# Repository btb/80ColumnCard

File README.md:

# 80ColumnCard
An 80-Column Card for the Apple II, II+, and clones.

This is mostly a clone of the Videx Videoterm, with some changes to reduce the number of chips needed.

[Interactive BOM](https://btb.github.io/80ColumnCard/hardware/80ColumnCard/bom/80ColumnCard_0.html)

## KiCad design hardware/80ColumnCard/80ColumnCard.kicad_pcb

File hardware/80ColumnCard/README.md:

# 80ColumnCard

## Construction notes

## RAM (U10)
U10 is designed to use a 6116 Static RAM chip, however there are multiple overlapping footprints available on the board in order for you to just use whatever 2K or larger SRAM is easiest for you to obtain. Consult the interactive BOM if you're not sure how to place the chip. Many larger chips however have the A11 pin where the 6116 has the /WE pin, so you'll have to cut and then re-solder the X21 jumper accordingly.

## Firmware ROM (U3)
U3 holds the 1K of firmware (e.g. "Videx Videoterm ROM 2.4.bin") and can be any EPROM from a 2758A up to a 27(C)512, depending on whatever you have available. A10 will be permanently tied low, and A11-A15 are all permanently tied high, so the code needs to go in the lower 1K of a 2716, or the lower half of the top 2K of any larger EPROM. (Or just repeat it enough times to fill up the whole thing)

## Character ROM (U20)
Any size from 2732 to 27C512 (27C080 on rev0) is pin-compatible, however the character generator subcircuit appears to be very sensitive to the speed of this EPROM. Character corruption occurs with EPROMs that are too fast, so 200ns or slower (higher number) is recommended.
Confirmed working are: M27C64-20, AM2732A-2.

This EPROM can hold one or two of the 2K [character sets](../../character_roms). A12-A15 are all permanently tied high, so only the top 4K of the EPROM is usable. The standard character set (e.g. "videx std 7x9 - top right.bin") goes in the lower 2K of that space, and any desired alternative character set (e.g. "videx inverse - top left.bin") goes in the upper 2K of that space.

## Other
Although many of the TTL LS chips can be substituted with members of newer logic families (ACT, for example), U2 (74LS02) U4 (74LS04) U6 (74LS00) U23 (74LS161) must be LS or other TTL (non-CMOS) families.

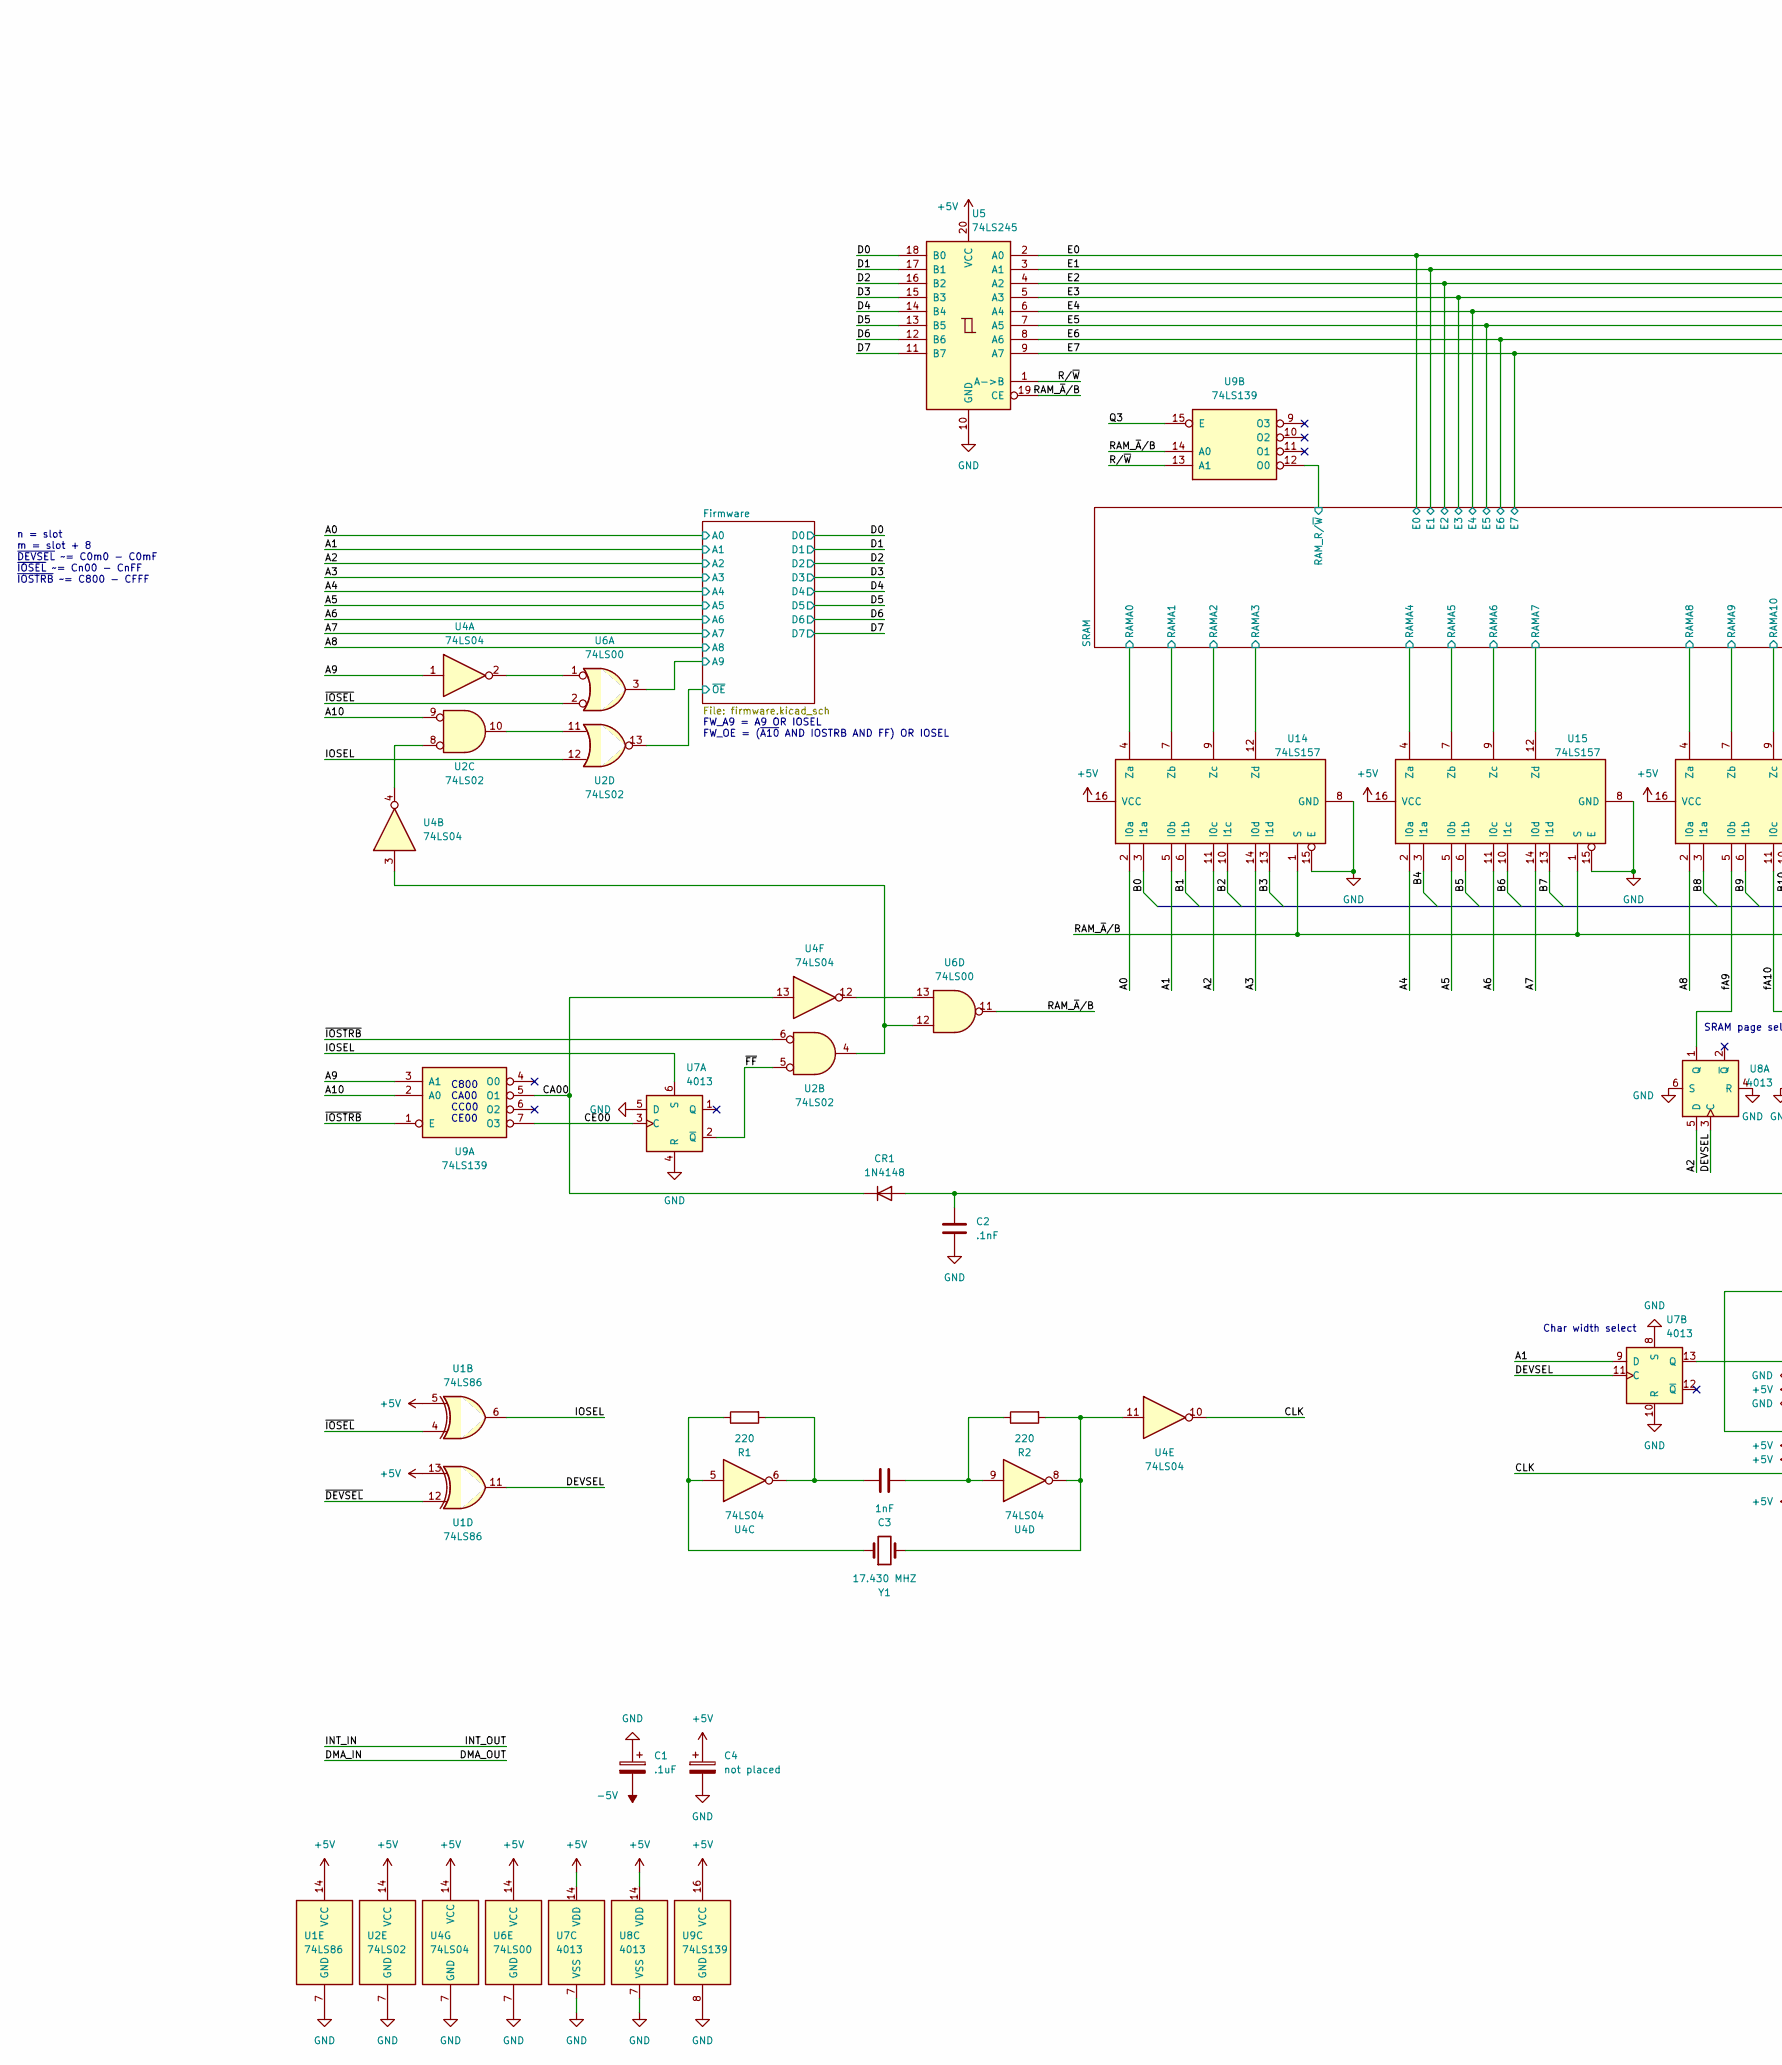
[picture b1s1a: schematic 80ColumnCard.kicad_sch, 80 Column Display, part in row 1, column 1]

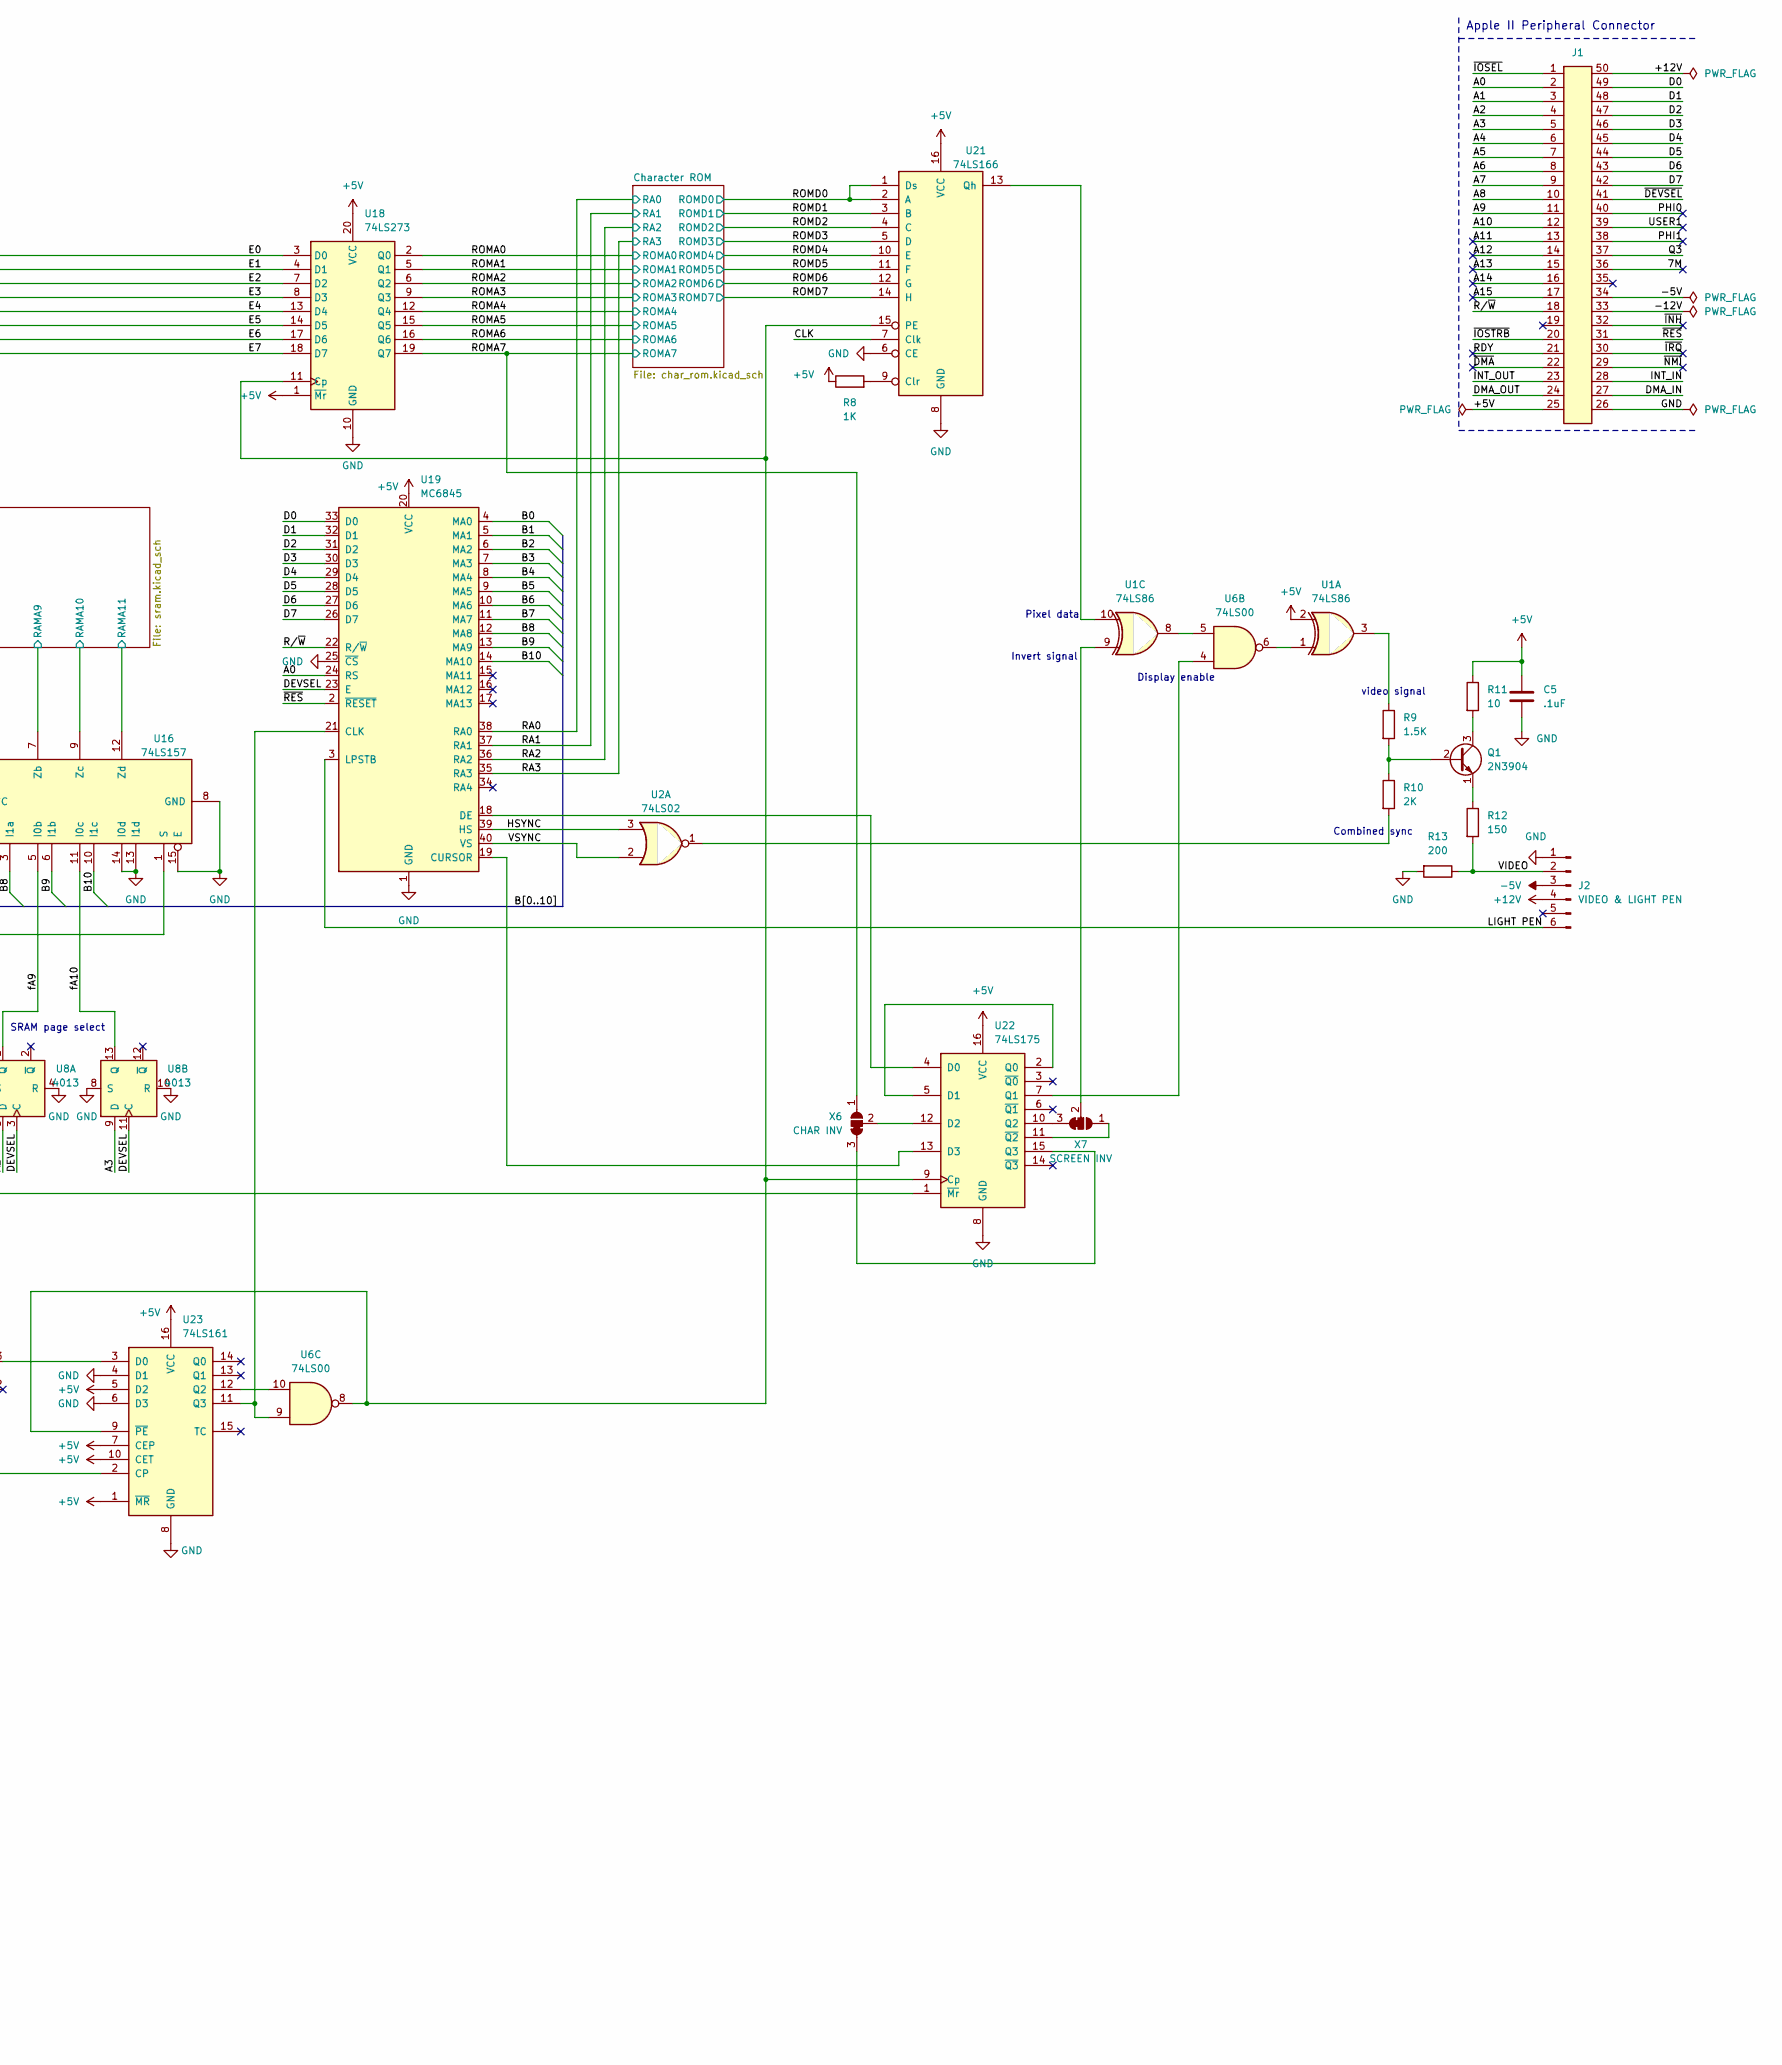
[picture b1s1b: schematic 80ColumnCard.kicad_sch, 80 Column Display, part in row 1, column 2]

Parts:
C1: .1uF; CP_Radial_Tantal_D4.5mm_P6.35mm
C2: .1nF; C_Axial_L2.6mm_D1.8mm_P6.35mm_Horizontal
C3: 1nF; C_Axial_L2.6mm_D1.8mm_P6.35mm_Horizontal
C4: not placed; CP_Radial_Tantal_D4.5mm_P6.35mm
C5: .1uF; C_Axial_L2.6mm_D1.8mm_P6.35mm_Horizontal
CR1: 1N4148; D_DO-35_SOD27_P10.16mm_Horizontal
J1: Apple II Expansion Bus; Apple II Expansion Edge Connector
J2: VIDEO & LIGHT PEN; PinHeader_1x06_P2.54mm_Horizontal
Q1: 2N3904; TO-92
R1, R2: 220; R_Axial_DIN0207_L6.3mm_D2.5mm_P10.16mm_Horizontal
R8: 1K; R_Axial_DIN0207_L6.3mm_D2.5mm_P10.16mm_Horizontal
R9: 1.5K; R_Axial_DIN0207_L6.3mm_D2.5mm_P10.16mm_Horizontal
R10: 2K; R_Axial_DIN0207_L6.3mm_D2.5mm_P10.16mm_Horizontal
R11: 10; R_Axial_DIN0207_L6.3mm_D2.5mm_P10.16mm_Horizontal
R12: 150; R_Axial_DIN0207_L6.3mm_D2.5mm_P10.16mm_Horizontal
R13: 200; R_Axial_DIN0207_L6.3mm_D2.5mm_P10.16mm_Horizontal
U1: 74LS86; DIP-14_W7.62mm
U2: 74LS02; DIP-14_W7.62mm
U4: 74LS04; DIP-14_W7.62mm
U5: 74LS245; DIP-20_W7.62mm
U6: 74LS00; DIP-14_W7.62mm
U7, U8: 4013; DIP-14_W7.62mm
U9: 74LS139; DIP-16_W7.62mm
U14, U15, U16: 74LS157; DIP-16_W7.62mm
U18: 74LS273; DIP-20_W7.62mm
U19: MC6845; DIP-40_W15.24mm
U21: 74LS166; DIP-16_W7.62mm
U22: 74LS175; DIP-16_W7.62mm
U23: 74LS161; DIP-16_W7.62mm
X6: CHAR INV; SolderJumper-3_Pie_Bridged23
X7: SCREEN INV; SolderJumper-3_Pie_Bridged23
Y1: 17.430 MHZ; Crystal_HC18-U_Horizontal

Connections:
+5V: C4.1, C5.1, J1.25 (+5V), R8.1, R11.1, U1.2, U1.5, U1.13, U1.14 (VCC), U2.14 (VCC), U4.14 (VCC), U5.20 (VCC), U6.14 (VCC), U7.14 (VDD), U8.14 (VDD), U9.16 (VCC), U14.16 (VCC), U15.16 (VCC), U16.16 (VCC), U18.1 (~Mr), U18.20 (VCC), U19.20 (VCC), U21.16 (VCC), U22.16 (VCC), U23.1 (~MR), U23.5 (D2), U23.7 (CEP), U23.10 (CET), U23.16 (VCC); also elsewhere on the board
+12V: J1.50 (-12V), J2.4
-5V: C1.2, J1.34 (-5V), J2.3
/7M: J1.36 (7M)
/-12V: J1.33 (-12V)
/A0: J1.2 (A00), U14.2 (I0a), U19.24 (RS); also elsewhere on the board
/A1: J1.3 (A01), U7.9 (D), U14.5 (I0b); also elsewhere on the board
/A2: J1.4 (A02), U8.5 (D), U14.11 (I0c); also elsewhere on the board
/A3: J1.5 (A03), U8.9 (D), U14.14 (I0d); also elsewhere on the board
/A4: J1.6 (A04), U15.2 (I0a); also elsewhere on the board
/A5: J1.7 (A05), U15.5 (I0b); also elsewhere on the board
/A6: J1.8 (A06), U15.11 (I0c); also elsewhere on the board
/A7: J1.9 (A07), U15.14 (I0d); also elsewhere on the board
/A8: J1.10 (A08), U16.2 (I0a); also elsewhere on the board
/A9: J1.11 (A09), U4.1, U9.3 (A1)
/A10: J1.12 (A10), U2.9, U9.2 (A0)
/A11: J1.13 (A11)
/A12: J1.14 (A12)
/A13: J1.15 (A13)
/A14: J1.16 (A14)
/A15: J1.17 (A15)
/B0: U14.3 (I1a), U19.4 (MA0)
/B1: U14.6 (I1b), U19.5 (MA1)
/B2: U14.10 (I1c), U19.6 (MA2)
/B3: U14.13 (I1d), U19.7 (MA3)
/B4: U15.3 (I1a), U19.8 (MA4)
/B5: U15.6 (I1b), U19.9 (MA5)
/B6: U15.10 (I1c), U19.10 (MA6)
/B7: U15.13 (I1d), U19.11 (MA7)
/B8: U16.3 (I1a), U19.12 (MA8)
/B9: U16.6 (I1b), U19.13 (MA9)
/B10: U16.10 (I1c), U19.14 (MA10)
/CA00: CR1.1 (K), U4.13, U9.5 (O1)
/CE00: U7.3 (C), U9.7 (O3)
/CLK: U4.10, U21.7 (Clk), U23.2 (CP)
/D0: J1.49 (D0), U5.18 (B0), U19.33 (D0); also elsewhere on the board
/D1: J1.48 (D1), U5.17 (B1), U19.32 (D1); also elsewhere on the board
/D2: J1.47 (D2), U5.16 (B2), U19.31 (D2); also elsewhere on the board
/D3: J1.46 (D3), U5.15 (B3), U19.30 (D3); also elsewhere on the board
/D4: J1.45 (D4), U5.14 (B4), U19.29 (D4); also elsewhere on the board
/D5: J1.44 (D5), U5.13 (B5), U19.28 (D5); also elsewhere on the board
/D6: J1.43 (D6), U5.12 (B6), U19.27 (D6); also elsewhere on the board
/D7: J1.42 (D7), U5.11 (B7), U19.26 (D7); also elsewhere on the board
/DEVSEL: U1.11, U7.11 (C), U8.3 (C), U8.11 (C), U19.23 (E)
/DMA_IN: J1.24 (DMA_OUT), J1.27 (DMA_IN)
/E0: U5.2 (A0), U18.3 (D0); also elsewhere on the board
/E1: U5.3 (A1), U18.4 (D1); also elsewhere on the board
/E2: U5.4 (A2), U18.7 (D2); also elsewhere on the board
/E3: U5.5 (A3), U18.8 (D3); also elsewhere on the board
/E4: U5.6 (A4), U18.13 (D4); also elsewhere on the board
/E5: U5.7 (A5), U18.14 (D5); also elsewhere on the board
/E6: U5.8 (A6), U18.17 (D6); also elsewhere on the board
/E7: U5.9 (A7), U18.18 (D7); also elsewhere on the board
/Firmware/A9: U6.3; also elsewhere on the board
/Firmware/~OE: U2.13; also elsewhere on the board
/HSYNC: U2.3, U19.39 (HS)
/INT_IN: J1.23 (INT_OUT), J1.28 (INT_IN)
/IOSEL: U1.6, U2.12, U7.6 (S)
/LIGHT PEN: J2.6, U19.3 (LPSTB)
/PHI0: J1.40 (PHI0)
/PHI1: J1.38 (PHI1)
/Q3: J1.37 (Q3), U9.15 (E)
/RA0: U19.38 (RA0); also elsewhere on the board
/RA1: U19.37 (RA1); also elsewhere on the board
/RA2: U19.36 (RA2); also elsewhere on the board
/RA3: U19.35 (RA3); also elsewhere on the board
/RAM_~A/B: U5.19 (CE), U6.11, U9.14 (A0), U14.1 (S), U15.1 (S), U16.1 (S)
/RDY: J1.21 (RDY)
/ROMA0: U18.2 (Q0); also elsewhere on the board
/ROMA1: U18.5 (Q1); also elsewhere on the board
/ROMA2: U18.6 (Q2); also elsewhere on the board
/ROMA3: U18.9 (Q3); also elsewhere on the board
/ROMA4: U18.12 (Q4); also elsewhere on the board
/ROMA5: U18.15 (Q5); also elsewhere on the board
/ROMA6: U18.16 (Q6); also elsewhere on the board
/ROMA7: U18.19 (Q7), X6.1 (A); also elsewhere on the board
/ROMD0: U21.1 (Ds), U21.2 (A); also elsewhere on the board
/ROMD1: U21.3 (B); also elsewhere on the board
/ROMD2: U21.4 (C); also elsewhere on the board
/ROMD3: U21.5 (D); also elsewhere on the board
/ROMD4: U21.10 (E); also elsewhere on the board
/ROMD5: U21.11 (F); also elsewhere on the board
/ROMD6: U21.12 (G); also elsewhere on the board
/ROMD7: U21.14 (H); also elsewhere on the board
/R/~W: J1.18 (R/~W), U5.1 (A->B), U9.13 (A1), U19.22 (R/~W)
/SRAM/RAMA0: U14.4 (Za); also elsewhere on the board
/SRAM/RAMA1: U14.7 (Zb); also elsewhere on the board
/SRAM/RAMA2: U14.9 (Zc); also elsewhere on the board
/SRAM/RAMA3: U14.12 (Zd); also elsewhere on the board
/SRAM/RAMA4: U15.4 (Za); also elsewhere on the board
/SRAM/RAMA5: U15.7 (Zb); also elsewhere on the board
/SRAM/RAMA6: U15.9 (Zc); also elsewhere on the board
/SRAM/RAMA7: U15.12 (Zd); also elsewhere on the board
/SRAM/RAMA8: U16.4 (Za); also elsewhere on the board
/SRAM/RAMA9: U16.7 (Zb); also elsewhere on the board
/SRAM/RAMA10: U16.9 (Zc); also elsewhere on the board
/SRAM/RAMA11: U16.12 (Zd); also elsewhere on the board
/SRAM/RAM_R/~W: U9.12 (O0); also elsewhere on the board
/USER1: J1.39 (USER1)
/VIDEO: J2.2, R12.2, R13.1
/VSYNC: U2.2, U19.40 (VS)
/fA9: U8.1 (Q), U16.5 (I0b)
/fA10: U8.13 (Q), U16.11 (I0c)
/~DEVSEL: J1.41 (~DEVICE_SELECT), U1.12
/~DMA: J1.22 (~DMA)
/~FF: U2.5, U7.2 (~Q)
/~INH: J1.32 (~INH)
/~IOSEL: J1.1 (~IO_SELECT), U1.4, U6.2
/~IOSTRB: J1.20 (~I/O_STROBE), U2.6, U9.1 (E)
/~IRQ: J1.30 (~IRQ)
/~NMI: J1.29 (~NMI)
/~RES: J1.31 (~RES), U19.2 (~RESET)
GND: C1.1, C2.2, C4.2, C5.2, J1.26 (GND), J2.1, R13.2, U1.7 (GND), U2.7 (GND), U4.7 (GND), U5.10 (GND), U6.7 (GND), U7.4 (R), U7.5 (D), U7.7 (VSS), U7.8 (S), U7.10 (R), U8.4 (R), U8.6 (S), U8.7 (VSS), U8.8 (S), U8.10 (R), U9.8 (GND), U14.8 (GND), U14.15 (E), U15.8 (GND), U15.15 (E), U16.8 (GND), U16.13 (I1d), U16.14 (I0d), U16.15 (E), U18.10 (GND), U19.1 (GND), U19.25 (~CS), U21.6 (CE), U21.8 (GND), U22.8 (GND), U23.4 (D1), U23.6 (D3), U23.8 (GND); also elsewhere on the board
unnamed: C2.1, CR1.2 (A), U22.1 (~Mr)
unnamed: C3.1, R1.2, U4.6
unnamed: C3.2, R2.1, U4.9
unnamed: Q1.1 (E), R12.1
unnamed: Q1.2 (B), R9.2, R10.1
unnamed: Q1.3 (C), R11.2
unnamed: R1.1, U4.5, Y1.1
unnamed: R2.2, U4.8, U4.11, Y1.2
unnamed: R8.2, U21.9 (Clr)
unnamed: R9.1, U1.3
unnamed: R10.2, U2.1
unnamed: U1.1, U6.6
unnamed: U1.8, U6.5
unnamed: U1.9, X7.2 (C)
unnamed: U1.10, U21.13 (Qh)
unnamed: U2.4, U4.3, U6.12
unnamed: U2.8, U4.4
unnamed: U2.10, U2.11
unnamed: U4.2, U6.1
unnamed: U4.12, U6.13
unnamed: U6.8, U18.11 (Cp), U21.15 (PE), U22.9 (Cp), U23.9 (~PE)
unnamed: U19.18 (DE), U22.4 (D0)
unnamed: U19.19 (CURSOR), U22.13 (D3)
unnamed: U6.9, U19.21 (CLK), U23.11 (Q3)
unnamed: U22.2 (Q0), U22.5 (D1)
unnamed: U6.4, U22.7 (Q1)
unnamed: U22.10 (Q2), X7.3 (B)
unnamed: U22.11 (~Q2), X7.1 (A)
unnamed: U22.12 (D2), X6.2 (C)
unnamed: U22.15 (Q3), X6.3 (B)
unnamed: U7.13 (Q), U23.3 (D0)
unnamed: U6.10, U23.12 (Q2)

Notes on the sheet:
Display enable
Apple II Peripheral Connector
Invert signal
n = slot m = slot + 8 ~{DEVSEL} ~= C0m0 - C0mF ~{IOSEL} ~= Cn00 - CnFF ~{IOSTRB} ~= C800 - CFFF
SRAM page select
Char width select
C800 CA00 CC00 CE00
Combined sync
video signal
Pixel data
FW_A9 = A9 OR IOSEL FW_OE = (~{A10} AND IOSTRB AND FF) OR IOSEL

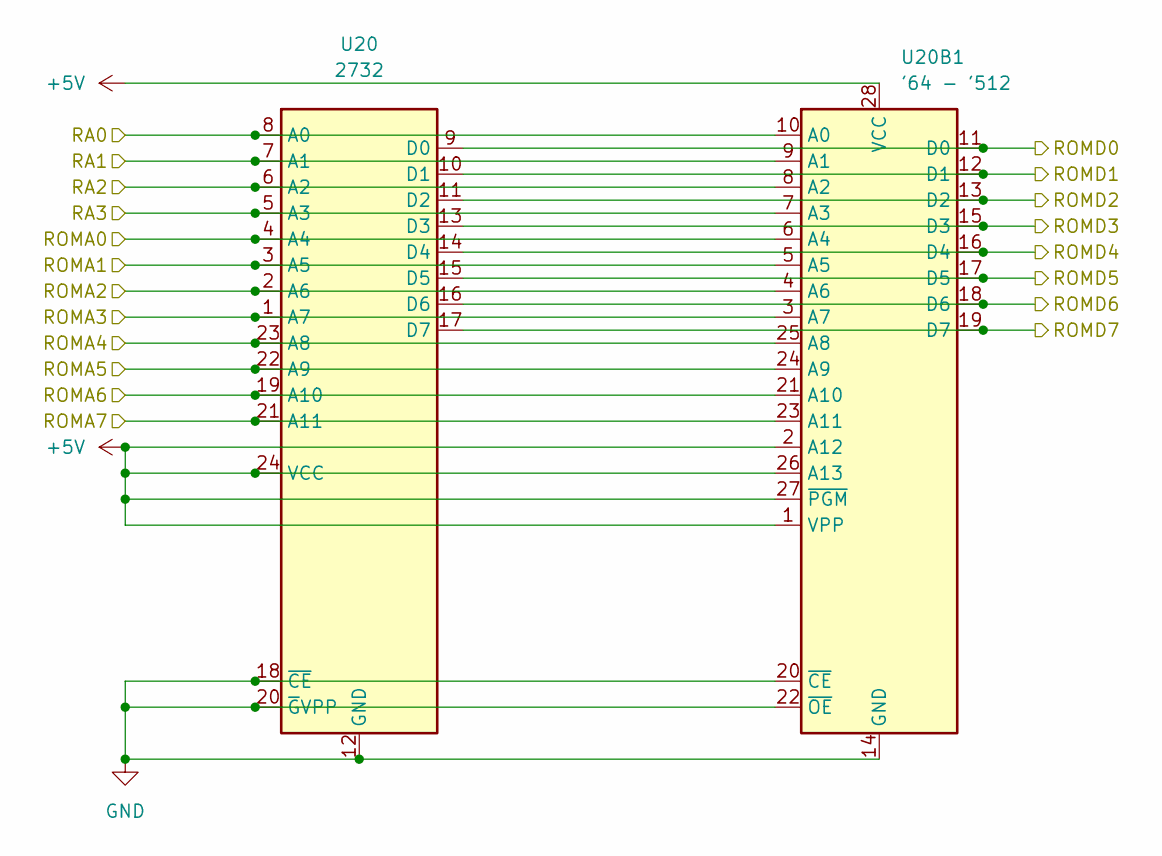
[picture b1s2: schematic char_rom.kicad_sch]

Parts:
U20: 2732; DIP-24_W15.24mm
U20B1: '64 - '512; DIP-28_W15.24mm

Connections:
+5V: U20.24 (VCC), U20B1.1 (VPP), U20B1.2 (A12), U20B1.26 (A13), U20B1.27 (~PGM), U20B1.28 (VCC); also elsewhere on the board
/RA0: U20.8 (A0), U20B1.10 (A0); also elsewhere on the board
/RA1: U20.7 (A1), U20B1.9 (A1); also elsewhere on the board
/RA2: U20.6 (A2), U20B1.8 (A2); also elsewhere on the board
/RA3: U20.5 (A3), U20B1.7 (A3); also elsewhere on the board
/ROMA0: U20.4 (A4), U20B1.6 (A4); also elsewhere on the board
/ROMA1: U20.3 (A5), U20B1.5 (A5); also elsewhere on the board
/ROMA2: U20.2 (A6), U20B1.4 (A6); also elsewhere on the board
/ROMA3: U20.1 (A7), U20B1.3 (A7); also elsewhere on the board
/ROMA4: U20.23 (A8), U20B1.25 (A8); also elsewhere on the board
/ROMA5: U20.22 (A9), U20B1.24 (A9); also elsewhere on the board
/ROMA6: U20.19 (A10), U20B1.21 (A10); also elsewhere on the board
/ROMA7: U20.21 (A11), U20B1.23 (A11); also elsewhere on the board
/ROMD0: U20.9 (D0), U20B1.11 (D0); also elsewhere on the board
/ROMD1: U20.10 (D1), U20B1.12 (D1); also elsewhere on the board
/ROMD2: U20.11 (D2), U20B1.13 (D2); also elsewhere on the board
/ROMD3: U20.13 (D3), U20B1.15 (D3); also elsewhere on the board
/ROMD4: U20.14 (D4), U20B1.16 (D4); also elsewhere on the board
/ROMD5: U20.15 (D5), U20B1.17 (D5); also elsewhere on the board
/ROMD6: U20.16 (D6), U20B1.18 (D6); also elsewhere on the board
/ROMD7: U20.17 (D7), U20B1.19 (D7); also elsewhere on the board
GND: U20.12 (GND), U20.18 (~CE), U20.20 (~GVPP), U20B1.14 (GND), U20B1.20 (~CE), U20B1.22 (~OE); also elsewhere on the board

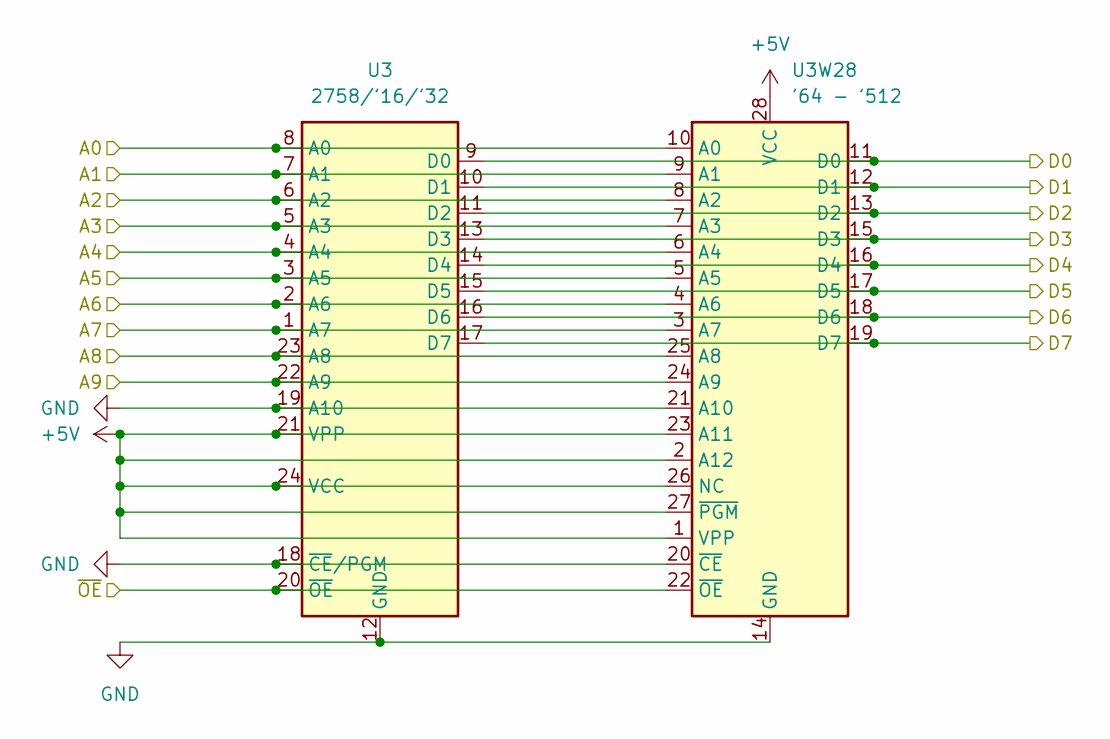
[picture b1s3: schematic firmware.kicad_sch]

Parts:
U3: 2758/'16/'32; DIP-24_W15.24mm
U3W28: '64 - '512; DIP-28_W15.24mm

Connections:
+5V: U3.21 (VPP), U3.24 (VCC), U3W28.1 (VPP), U3W28.2 (A12), U3W28.23 (A11), U3W28.26 (NC), U3W28.27 (~PGM), U3W28.28 (VCC); also elsewhere on the board
/A0: U3.8 (A0), U3W28.10 (A0); also elsewhere on the board
/A1: U3.7 (A1), U3W28.9 (A1); also elsewhere on the board
/A2: U3.6 (A2), U3W28.8 (A2); also elsewhere on the board
/A3: U3.5 (A3), U3W28.7 (A3); also elsewhere on the board
/A4: U3.4 (A4), U3W28.6 (A4); also elsewhere on the board
/A5: U3.3 (A5), U3W28.5 (A5); also elsewhere on the board
/A6: U3.2 (A6), U3W28.4 (A6); also elsewhere on the board
/A7: U3.1 (A7), U3W28.3 (A7); also elsewhere on the board
/A8: U3.23 (A8), U3W28.25 (A8); also elsewhere on the board
/D0: U3.9 (D0), U3W28.11 (D0); also elsewhere on the board
/D1: U3.10 (D1), U3W28.12 (D1); also elsewhere on the board
/D2: U3.11 (D2), U3W28.13 (D2); also elsewhere on the board
/D3: U3.13 (D3), U3W28.15 (D3); also elsewhere on the board
/D4: U3.14 (D4), U3W28.16 (D4); also elsewhere on the board
/D5: U3.15 (D5), U3W28.17 (D5); also elsewhere on the board
/D6: U3.16 (D6), U3W28.18 (D6); also elsewhere on the board
/D7: U3.17 (D7), U3W28.19 (D7); also elsewhere on the board
/Firmware/A9: U3.22 (A9), U3W28.24 (A9); also elsewhere on the board
/Firmware/~OE: U3.20 (~OE), U3W28.22 (~OE); also elsewhere on the board
GND: U3.12 (GND), U3.18 (~CE/PGM), U3.19 (A10), U3W28.14 (GND), U3W28.20 (~CE), U3W28.21 (A10); also elsewhere on the board

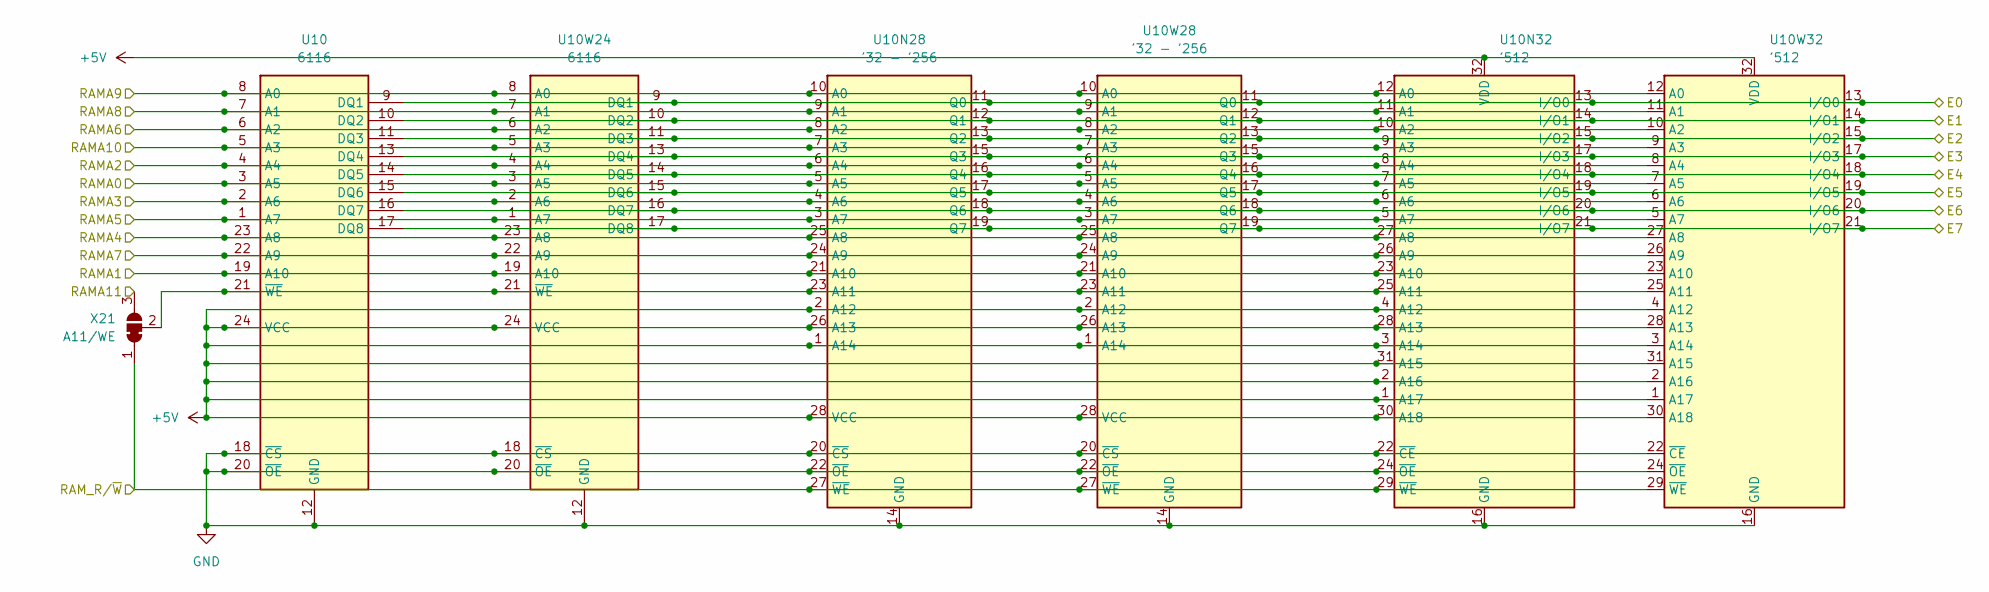
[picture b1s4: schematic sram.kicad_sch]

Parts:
U10: 6116; DIP-24_W7.62mm
U10N28: '32 - '256; DIP-28_W7.62mm
U10N32: '512; DIP-32_W7.62mm
U10W24: 6116; DIP-24_W15.24mm
U10W28: '32 - '256; DIP-28_W15.24mm
U10W32: '512; DIP-32_W15.24mm
X21: A11/WE; SolderJumper-3_Pie_Bridged12

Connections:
+5V: U10.24 (VCC), U10N28.1 (A14), U10N28.2 (A12), U10N28.26 (A13), U10N28.28 (VCC), U10N32.1 (A17), U10N32.2 (A16), U10N32.3 (A14), U10N32.4 (A12), U10N32.28 (A13), U10N32.30 (A18), U10N32.31 (A15), U10N32.32 (VDD), U10W24.24 (VCC), U10W28.1 (A14), U10W28.2 (A12), U10W28.26 (A13), U10W28.28 (VCC), U10W32.1 (A17), U10W32.2 (A16), U10W32.3 (A14), U10W32.4 (A12), U10W32.28 (A13), U10W32.30 (A18), U10W32.31 (A15), U10W32.32 (VDD); also elsewhere on the board
/E0: U10.9 (DQ1), U10N28.11 (Q0), U10N32.13 (I/O0), U10W24.9 (DQ1), U10W28.11 (Q0), U10W32.13 (I/O0); also elsewhere on the board
/E1: U10.10 (DQ2), U10N28.12 (Q1), U10N32.14 (I/O1), U10W24.10 (DQ2), U10W28.12 (Q1), U10W32.14 (I/O1); also elsewhere on the board
/E2: U10.11 (DQ3), U10N28.13 (Q2), U10N32.15 (I/O2), U10W24.11 (DQ3), U10W28.13 (Q2), U10W32.15 (I/O2); also elsewhere on the board
/E3: U10.13 (DQ4), U10N28.15 (Q3), U10N32.17 (I/O3), U10W24.13 (DQ4), U10W28.15 (Q3), U10W32.17 (I/O3); also elsewhere on the board
/E4: U10.14 (DQ5), U10N28.16 (Q4), U10N32.18 (I/O4), U10W24.14 (DQ5), U10W28.16 (Q4), U10W32.18 (I/O4); also elsewhere on the board
/E5: U10.15 (DQ6), U10N28.17 (Q5), U10N32.19 (I/O5), U10W24.15 (DQ6), U10W28.17 (Q5), U10W32.19 (I/O5); also elsewhere on the board
/E6: U10.16 (DQ7), U10N28.18 (Q6), U10N32.20 (I/O6), U10W24.16 (DQ7), U10W28.18 (Q6), U10W32.20 (I/O6); also elsewhere on the board
/E7: U10.17 (DQ8), U10N28.19 (Q7), U10N32.21 (I/O7), U10W24.17 (DQ8), U10W28.19 (Q7), U10W32.21 (I/O7); also elsewhere on the board
/SRAM/RAMA0: U10.3 (A5), U10N28.5 (A5), U10N32.7 (A5), U10W24.3 (A5), U10W28.5 (A5), U10W32.7 (A5); also elsewhere on the board
/SRAM/RAMA1: U10.19 (A10), U10N28.21 (A10), U10N32.23 (A10), U10W24.19 (A10), U10W28.21 (A10), U10W32.23 (A10); also elsewhere on the board
/SRAM/RAMA2: U10.4 (A4), U10N28.6 (A4), U10N32.8 (A4), U10W24.4 (A4), U10W28.6 (A4), U10W32.8 (A4); also elsewhere on the board
/SRAM/RAMA3: U10.2 (A6), U10N28.4 (A6), U10N32.6 (A6), U10W24.2 (A6), U10W28.4 (A6), U10W32.6 (A6); also elsewhere on the board
/SRAM/RAMA4: U10.23 (A8), U10N28.25 (A8), U10N32.27 (A8), U10W24.23 (A8), U10W28.25 (A8), U10W32.27 (A8); also elsewhere on the board
/SRAM/RAMA5: U10.1 (A7), U10N28.3 (A7), U10N32.5 (A7), U10W24.1 (A7), U10W28.3 (A7), U10W32.5 (A7); also elsewhere on the board
/SRAM/RAMA6: U10.6 (A2), U10N28.8 (A2), U10N32.10 (A2), U10W24.6 (A2), U10W28.8 (A2), U10W32.10 (A2); also elsewhere on the board
/SRAM/RAMA7: U10.22 (A9), U10N28.24 (A9), U10N32.26 (A9), U10W24.22 (A9), U10W28.24 (A9), U10W32.26 (A9); also elsewhere on the board
/SRAM/RAMA8: U10.7 (A1), U10N28.9 (A1), U10N32.11 (A1), U10W24.7 (A1), U10W28.9 (A1), U10W32.11 (A1); also elsewhere on the board
/SRAM/RAMA9: U10.8 (A0), U10N28.10 (A0), U10N32.12 (A0), U10W24.8 (A0), U10W28.10 (A0), U10W32.12 (A0); also elsewhere on the board
/SRAM/RAMA10: U10.5 (A3), U10N28.7 (A3), U10N32.9 (A3), U10W24.5 (A3), U10W28.7 (A3), U10W32.9 (A3); also elsewhere on the board
/SRAM/RAMA11: X21.3 (B); also elsewhere on the board
/SRAM/RAM_R/~W: U10N28.27 (~WE), U10N32.29 (~WE), U10W28.27 (~WE), U10W32.29 (~WE), X21.1 (A); also elsewhere on the board
GND: U10.12 (GND), U10.18 (~CS), U10.20 (~OE), U10N28.14 (GND), U10N28.20 (~CS), U10N28.22 (~OE), U10N32.16 (GND), U10N32.22 (~CE), U10N32.24 (~OE), U10W24.12 (GND), U10W24.18 (~CS), U10W24.20 (~OE), U10W28.14 (GND), U10W28.20 (~CS), U10W28.22 (~OE), U10W32.16 (GND), U10W32.22 (~CE), U10W32.24 (~OE); also elsewhere on the board
unnamed: U10.21 (~WE), U10N28.23 (A11), U10N32.25 (A11), U10W24.21 (~WE), U10W28.23 (A11), U10W32.25 (A11), X21.2 (C)

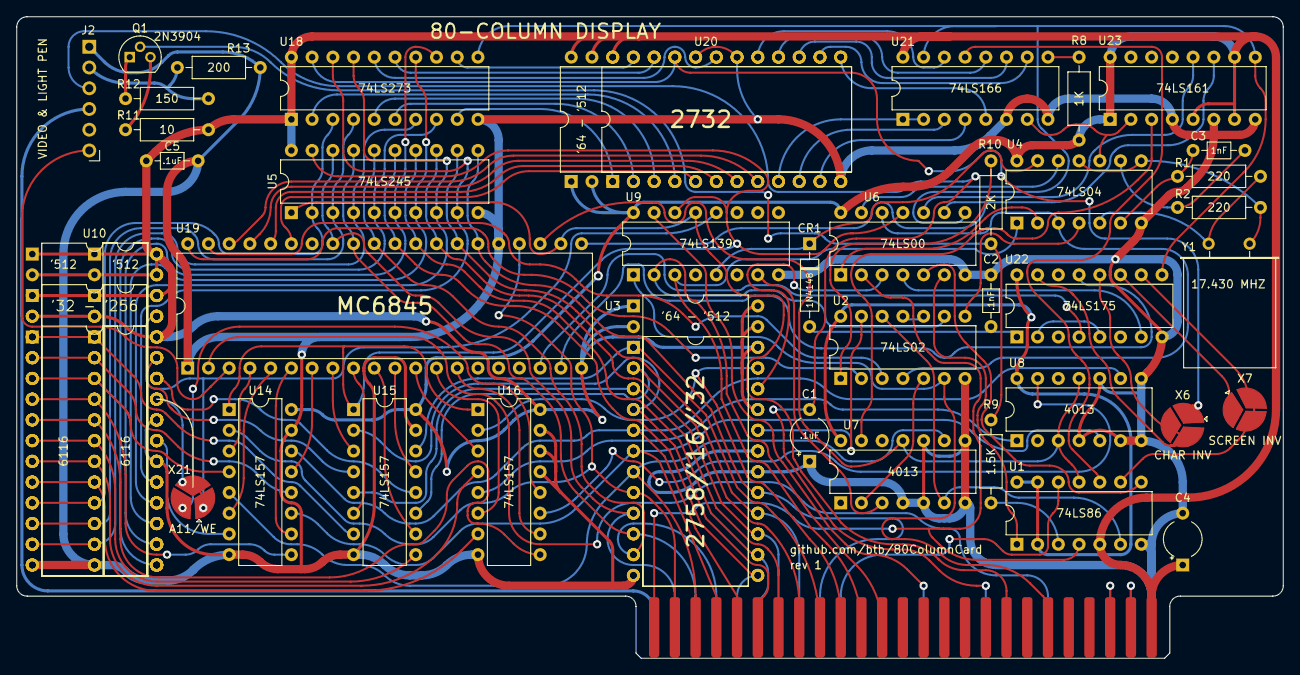
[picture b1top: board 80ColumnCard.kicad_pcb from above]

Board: 2 copper layers, 155.2 x 78.6 mm, 47 parts (0 on the bottom side), 131 nets.
